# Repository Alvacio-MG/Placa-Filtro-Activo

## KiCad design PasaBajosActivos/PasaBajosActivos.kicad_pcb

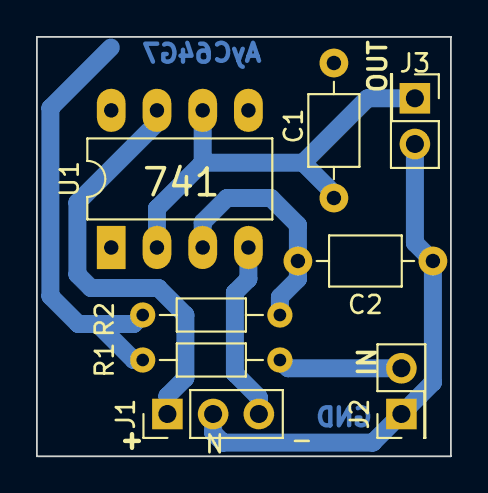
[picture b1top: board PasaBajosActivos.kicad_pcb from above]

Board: 2 copper layers, 23.0 x 23.3 mm, 8 parts (0 on the bottom side), 7 nets.

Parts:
C1, C2: C; C_Axial_L3.8mm_D2.6mm_P7.50mm_Horizontal
J1: Alimentacion; PinHeader_1x03_P2.54mm_Vertical
J2: VIN; PinHeader_2x01_P2.54mm_Vertical
J3: VOUT; PinHeader_2x01_P2.54mm_Vertical
R1, R2: R; R_Axial_DIN0204_L3.6mm_D1.6mm_P7.62mm_Horizontal
U1: LM741; DIP-8_W7.62mm_LongPads

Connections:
GND: C2.1, J1.2, J2.1, J3.2
unnamed: C1.1, R1.2, R2.1
unnamed: J2.2, R1.1
unnamed: C1.2, J3.1, U1.2 (-), U1.6
unnamed: C2.2, R2.2, U1.3 (+)
VCC: J1.1, U1.7 (V+)
VEE: J1.3, U1.4 (V-)

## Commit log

2024-09-30 Subida de los archivos de la placa (KiCad) y CNC (Flatcam)
